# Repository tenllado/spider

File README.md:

# Spider board

A simple board for a digital electronics laboratory. It is ment to use with a
breadboard, the board is used to generate inputs for digital circuits and show
outputs of them lighting the leds.

The board contains:
- 8 switches for 8 digital inputs
- 8 leds for 8 digital outputs
- 1 push button to generate a clock signal

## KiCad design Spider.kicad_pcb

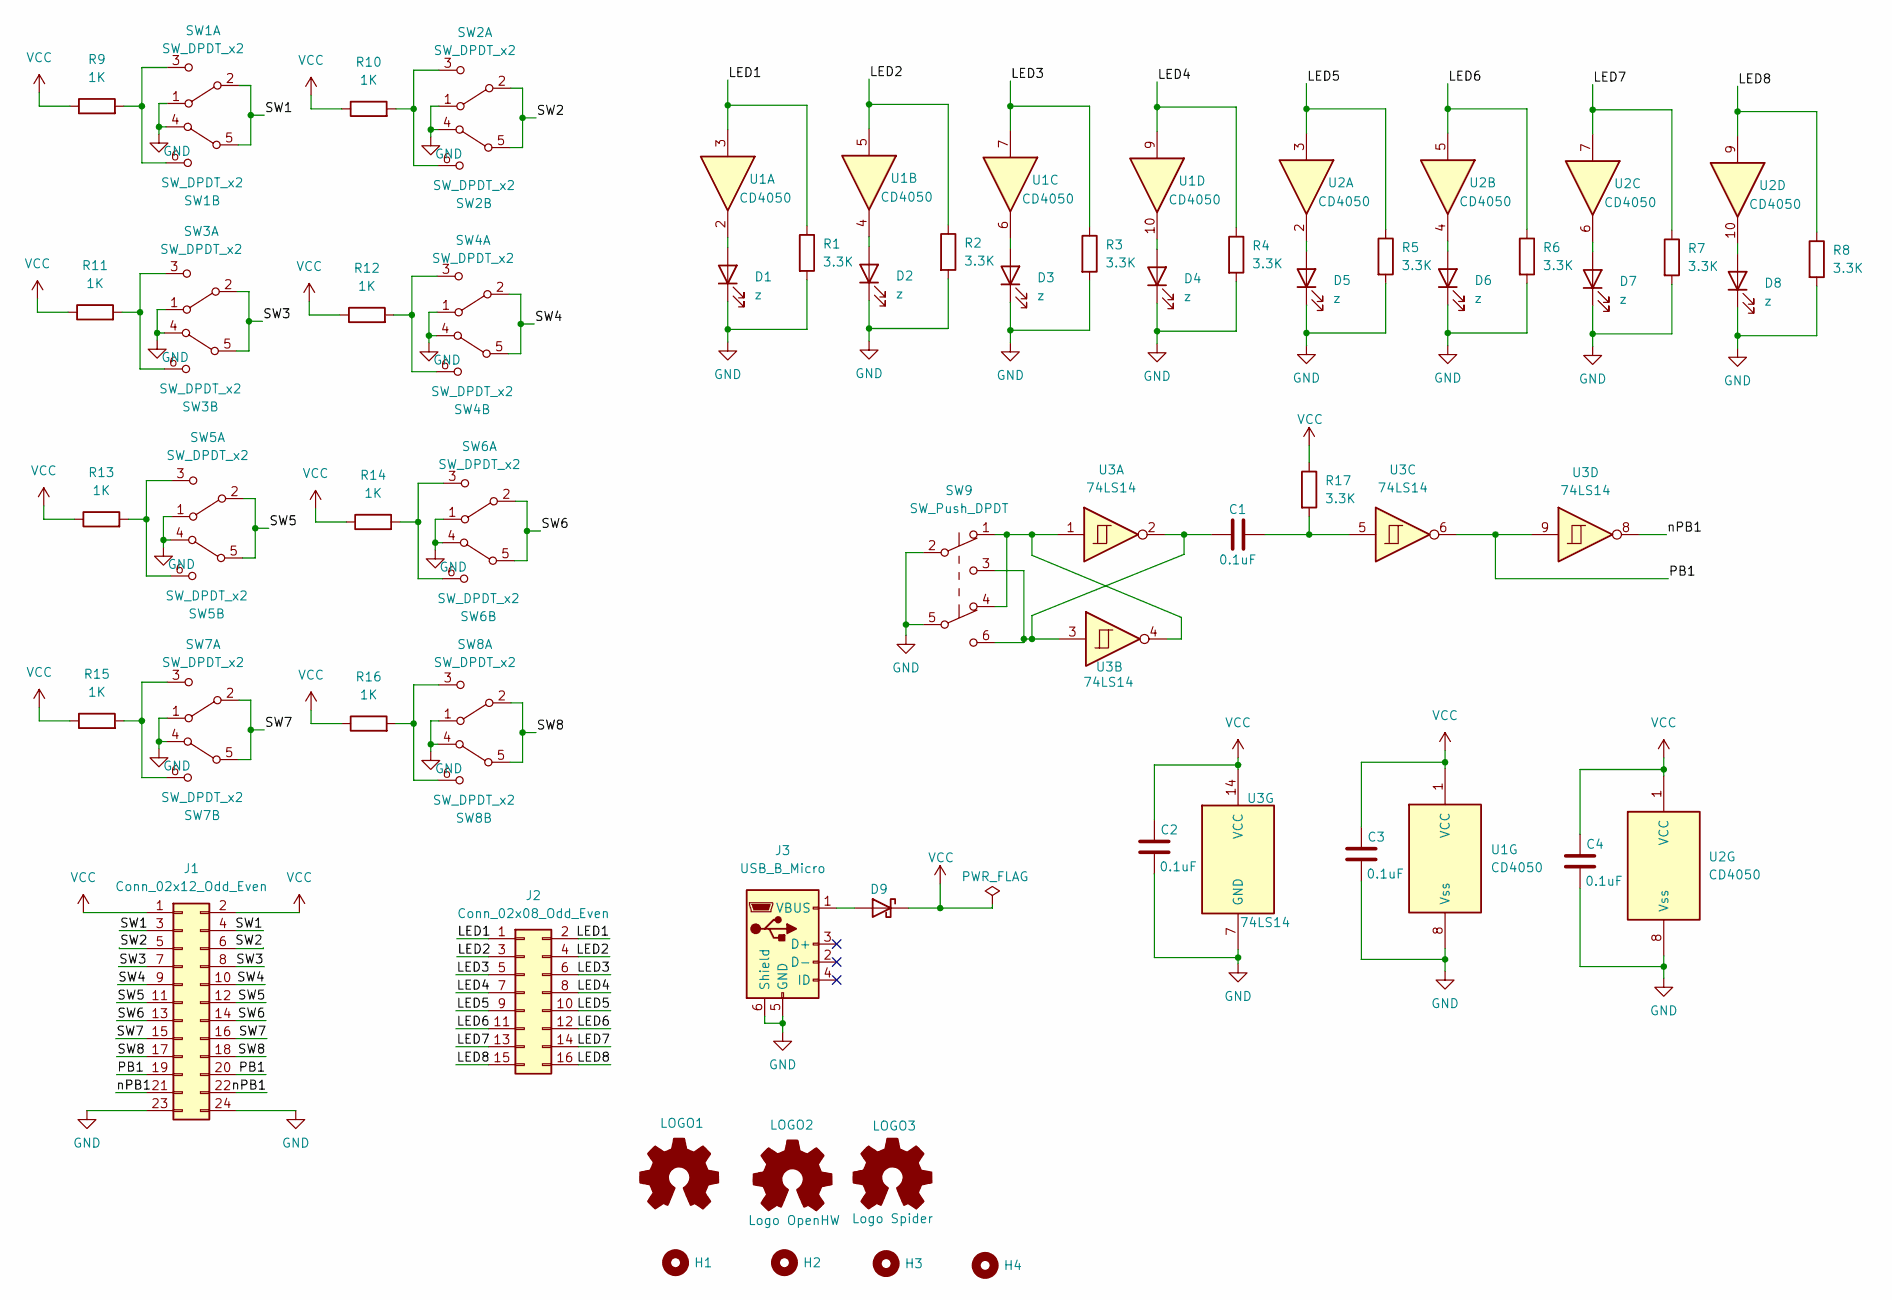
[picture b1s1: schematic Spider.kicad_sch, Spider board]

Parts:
C1, C2, C3, C4: 0.1uF; C_0603_1608Metric_Pad1.08x0.95mm_HandSolder; MPN C0603C104J4RACTU
D1, D2, D3, D4, D5, D6, D7, D8: z; LED_0603_1608Metric_Pad1.05x0.95mm_HandSolder; MPN LTST-C193KRKT-2A
D9: D_SMA; MPN B340AE-13
H1, H2, H3, H4: (no value)
J1: Conn_02x12_Odd_Even; PinHeader_2x12_P2.54mm_Vertical_SMD; MPN SSM-112-L-DV
J2: Conn_02x08_Odd_Even; PinHeader_2x08_P2.54mm_Vertical_SMD; MPN SSM-108-F-DV-K-TR
J3: USB_B_Micro; USB_Micro-B_Amphenol_10103594-0001LF_Horizontal; MPN 10103594-0001LF
LOGO1: (no value)
LOGO2: Logo OpenHW; OSHW-Logo_7.5x8mm_SilkScreen
LOGO3: Logo Spider; spider_logo
R1, R2, R3, R4, R5, R6, R7, R8, R17: 3.3K; R_0805_2012Metric_Pad1.20x1.40mm_HandSolder; MPN ERJ-PB6B3303V
R9, R10, R11, R12, R13, R14, R15, R16: 1K; R_0805_2012Metric_Pad1.20x1.40mm_HandSolder; MPN ERA-6AEB102V
SW1, SW2, SW3, SW4, SW5, SW6, SW7, SW8: SW_DPDT_x2; SW_DPDT; MPN JS202011SCQN
SW9: SW_Push_DPDT; TL2230OAF140; MPN TL2230OAF140
U1, U2: CD4050; SOIC-16W_7.5x10.3mm_P1.27mm; MPN CD4050BDW
U3: 74LS14; SSOP-14_5.3x6.2mm_P0.65mm; MPN SN74LS14DBR

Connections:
/LED1: J2.1, J2.2, R1.1, U1.3
/LED2: J2.3, J2.4, R2.1, U1.5
/LED3: J2.5, J2.6, R3.1, U1.7
/LED4: J2.7, J2.8, R4.1, U1.9
/LED5: J2.9, J2.10, R5.1, U2.3
/LED6: J2.11, J2.12, R6.1, U2.5
/LED7: J2.13, J2.14, R7.1, U2.7
/LED8: J2.15, J2.16, R8.1, U2.9
/PB1: J1.19, J1.20, U3.6, U3.9
/SW1: J1.3, J1.4, SW1.2 (B), SW1.5 (B)
/SW2: J1.5, J1.6, SW2.2 (B), SW2.5 (B)
/SW3: J1.7, J1.8, SW3.2 (B), SW3.5 (B)
/SW4: J1.9, J1.10, SW4.2 (B), SW4.5 (B)
/SW5: J1.11, J1.12, SW5.2 (B), SW5.5 (B)
/SW6: J1.13, J1.14, SW6.2 (B), SW6.5 (B)
/SW7: J1.15, J1.16, SW7.2 (B), SW7.5 (B)
/SW8: J1.17, J1.18, SW8.2 (B), SW8.5 (B)
/nPB1: J1.21, J1.22, U3.8
GND: C2.2, C3.2, C4.2, D1.1 (K), D2.1 (K), D3.1 (K), D4.1 (K), D5.1 (K), D6.1 (K), D7.1 (K), D8.1 (K), J1.23, J1.24, J3.5 (GND), J3.6 (Shield), R1.2, R2.2, R3.2, R4.2, R5.2, R6.2, R7.2, R8.2, SW1.1 (A), SW1.4 (A), SW2.1 (A), SW2.4 (A), SW3.1 (A), SW3.4 (A), SW4.1 (A), SW4.4 (A), SW5.1 (A), SW5.4 (A), SW6.1 (A), SW6.4 (A), SW7.1 (A), SW7.4 (A), SW8.1 (A), SW8.4 (A), SW9.2 (B), SW9.5 (B), U1.8 (Vss), U2.8 (Vss), U3.7 (GND)
unnamed: C1.1, SW9.3 (C), SW9.6 (C), U3.2, U3.3
unnamed: C1.2, R17.2, U3.5
unnamed: D1.2 (A), U1.2
unnamed: D2.2 (A), U1.4
unnamed: D3.2 (A), U1.6
unnamed: D4.2 (A), U1.10
unnamed: D5.2 (A), U2.2
unnamed: D6.2 (A), U2.4
unnamed: D7.2 (A), U2.6
unnamed: D8.2 (A), U2.10
unnamed: D9.2 (A), J3.1 (VBUS)
unnamed: R9.2, SW1.3 (C), SW1.6 (C)
unnamed: R10.2, SW2.3 (C), SW2.6 (C)
unnamed: R11.2, SW3.3 (C), SW3.6 (C)
unnamed: R12.2, SW4.3 (C), SW4.6 (C)
unnamed: R13.2, SW5.3 (C), SW5.6 (C)
unnamed: R14.2, SW6.3 (C), SW6.6 (C)
unnamed: R15.2, SW7.3 (C), SW7.6 (C)
unnamed: R16.2, SW8.3 (C), SW8.6 (C)
unnamed: SW9.1 (A), SW9.4 (A), U3.1, U3.4
VCC: C2.1, C3.1, C4.1, D9.1 (K), J1.1, J1.2, R9.1, R10.1, R11.1, R12.1, R13.1, R14.1, R15.1, R16.1, R17.1, U1.1 (VCC), U2.1 (VCC), U3.14 (VCC)

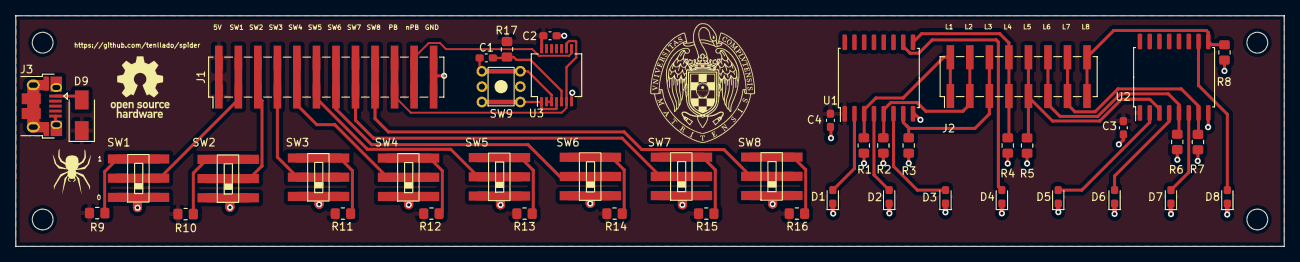
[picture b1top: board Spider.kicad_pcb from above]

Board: 2 copper layers, 165.0 x 30.0 mm, 52 parts (0 on the bottom side), 40 nets.

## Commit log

2022-06-03 files for the project rev1.0
2022-06-03 ignore png files in logo
2022-06-03 1-0 mark on silkscreen
2022-06-03 url of project to silkscreen
2022-06-06 split inputs and outputs, mounting holes, smd sockets
2022-06-06 remove small tracks, pcb erc warnings
